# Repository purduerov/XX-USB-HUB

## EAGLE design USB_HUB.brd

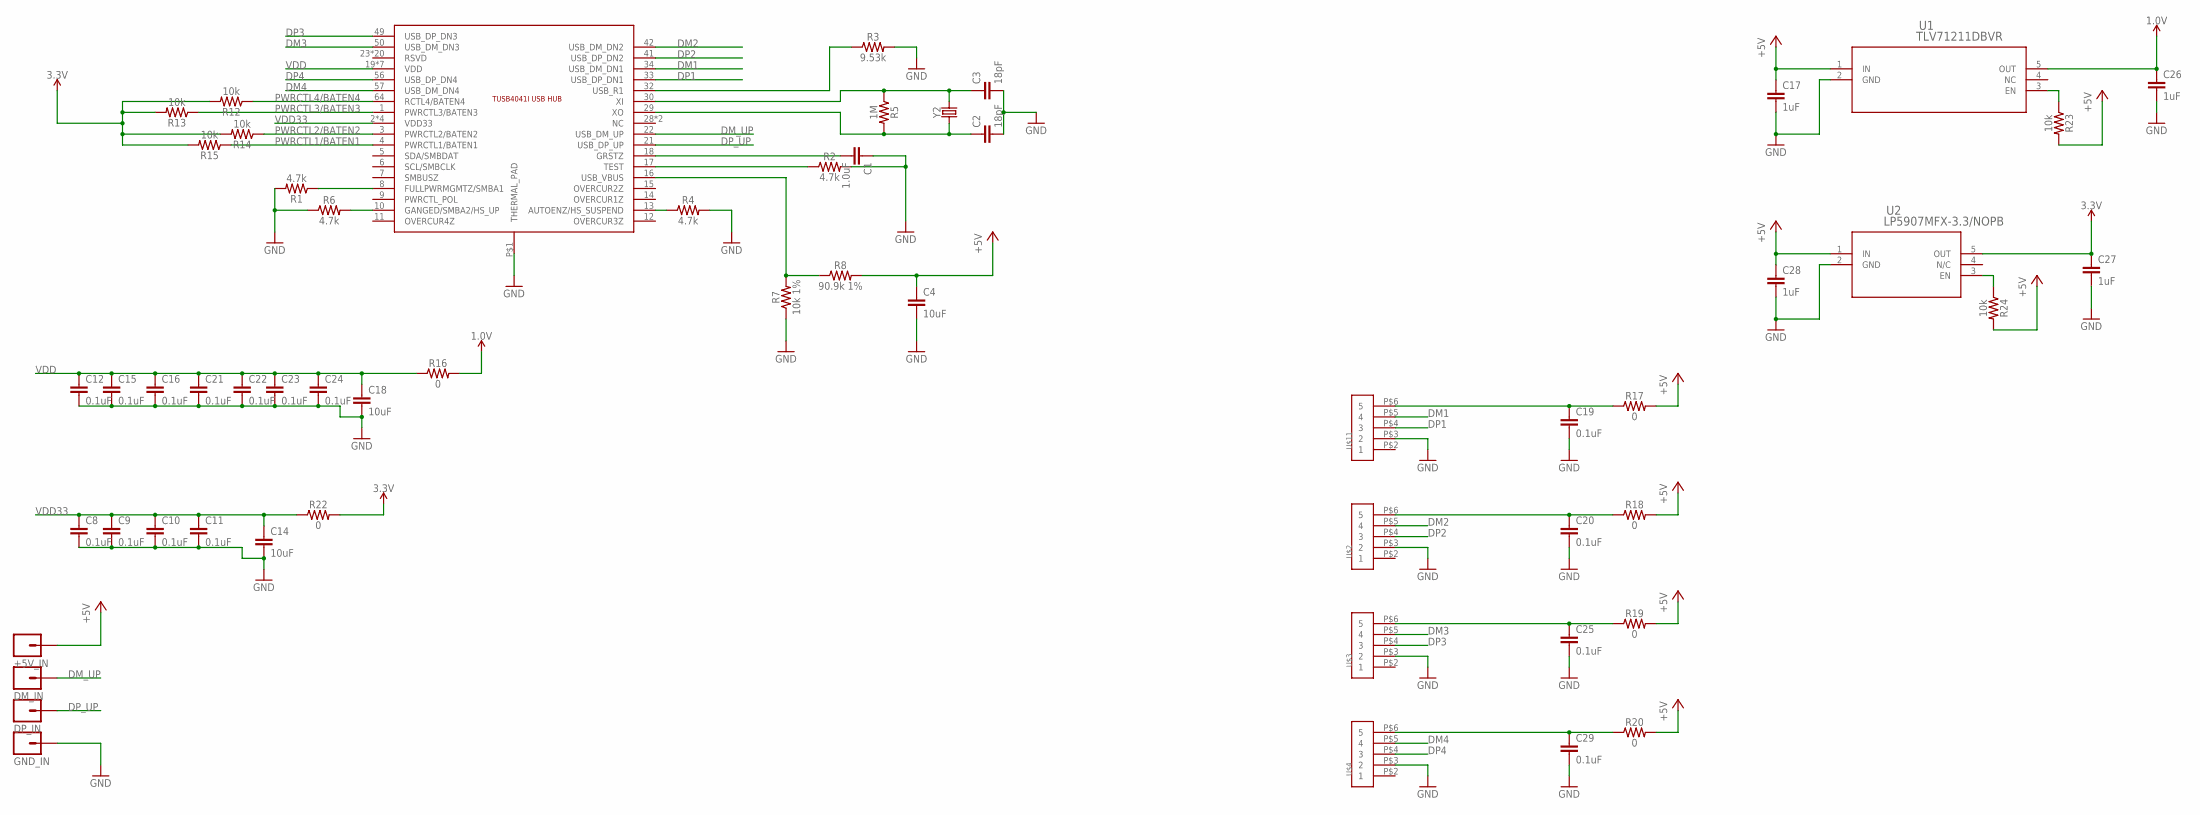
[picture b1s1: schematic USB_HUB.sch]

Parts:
+5V_IN: M01PTH; 1X01
C1: 1.0uF; 0603
C2, C3: 18pF; 0603
C4, C14, C18: 10uF; 0805
C8, C9, C10, C11, C12, C15, C16, C19, C20, C21, C22, C23, C24, C25, C29: 0.1uF; 0603
C17, C26, C27, C28: 1uF; 0603
DM_IN: M01PTH; 1X01
DP_IN: M01PTH; 1X01
GND_IN: M01PTH; 1X01
R1, R2, R4, R6: 4.7k; 0603
R3: 9.53k; 0603
R5: 1M; 0603
R7: 10k 1%; 0603
R8: 90.9k 1%; 0603
R12, R13, R14, R15, R23, R24: 10k; 0603
R16, R17, R18, R19, R20, R22: 0; 0805
U1: TLV71211DBVR; DBV5
U2: LP5907MFX-3.3/NOPB; DBV5
U$1: TUSB4041I
U$2, U$3, U$4, U$11: T2I5P
Y2: CRYSTALPTH-HC49US; HC49US

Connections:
1.0V: C26.1, R16.2, U1.5 (OUT)
3.3V: C27.1, R12.2, R13.2, R14.2, R15.2, R22.2, U2.5 (OUT)
+5V: +5V_IN.1, C4.1, C17.1, C28.1, R8.2, R17.2, R18.2, R19.2, R20.2, R23.2, R24.2, U1.1 (IN), U2.1 (IN)
DM1: U$1.34 (USB_DM_DN1), U$11.P$5 (4)
DM2: U$1.42 (USB_DM_DN2), U$2.P$5 (4)
DM3: U$1.50 (USB_DM_DN3), U$3.P$5 (4)
DM4: U$1.57 (USB_DM_DN4), U$4.P$5 (4)
DM_UP: DM_IN.1, U$1.22 (USB_DM_UP)
DP1: U$1.33 (USB_DP_DN1), U$11.P$4 (3)
DP2: U$1.41 (USB_DP_DN2), U$2.P$4 (3)
DP3: U$1.49 (USB_DP_DN3), U$3.P$4 (3)
DP4: U$1.56 (USB_DP_DN4), U$4.P$4 (3)
DP_UP: DP_IN.1, U$1.21 (USB_DP_UP)
GND: C1.1, C2.2, C3.2, C4.2, C8.2, C9.2, C10.2, C11.2, C12.2, C14.2, C15.2, C16.2, C17.2, C18.2, C19.2, C20.2, C21.2, C22.2, C23.2, C24.2, C25.2, C26.2, C27.2, C28.2, C29.2, GND_IN.1, R1.2, R2.2, R3.2, R4.2, R6.1, R7.1, U1.2 (GND), U2.2 (GND), U$1.P$1 (THERMAL_PAD), U$2.P$3 (2), U$3.P$3 (2), U$4.P$3 (2), U$11.P$3 (2)
unnamed: C1.2, U$1.18 (GRSTZ)
unnamed: R3.1, U$1.32 (USB_R1)
unnamed: R2.1, U$1.17 (TEST)
unnamed: R4.1, U$1.13 (AUTOENZ/HS_SUSPEND)
unnamed: C3.1, R5.1, U$1.30 (XI), Y2.2
unnamed: C2.1, R5.2, U$1.29 (XO), Y2.1
unnamed: R1.1, U$1.8 (FULLPWRMGMTZ/SMBA1)
unnamed: R6.2, U$1.10 (GANGED/SMBA2/HS_UP)
unnamed: R7.2, R8.1, U$1.16 (USB_VBUS)
unnamed: R23.1, U1.3 (EN)
unnamed: R24.1, U2.3 (EN)
PWRCTL1/BATEN1: R15.1, U$1.4 (PWRCTL1/BATEN1)
PWRCTL2/BATEN2: R14.1, U$1.3 (PWRCTL2/BATEN2)
PWRCTL3/BATEN3: R13.1, U$1.1 (PWRCTL3/BATEN3)
PWRCTL4/BATEN4: R12.1, U$1.64 (RCTL4/BATEN4)
USB1_+5V: C19.1, R17.1, U$11.P$6 (5)
USB2_+5V: C20.1, R18.1, U$2.P$6 (5)
USB3_+5V: C25.1, R19.1, U$3.P$6 (5)
USB4_+5V: C29.1, R20.1, U$4.P$6 (5)
VDD: C12.1, C15.1, C16.1, C18.1, C21.1, C22.1, C23.1, C24.1, R16.1, U$1.19 (VDD), U$1.25 (VDD), U$1.37 (VDD), U$1.45 (VDD), U$1.53 (VDD), U$1.60 (VDD), U$1.63 (VDD)
VDD33: C8.1, C9.1, C10.1, C11.1, C14.1, R22.1, U$1.2 (VDD33), U$1.20 (VDD33), U$1.31 (VDD33), U$1.48 (VDD33)

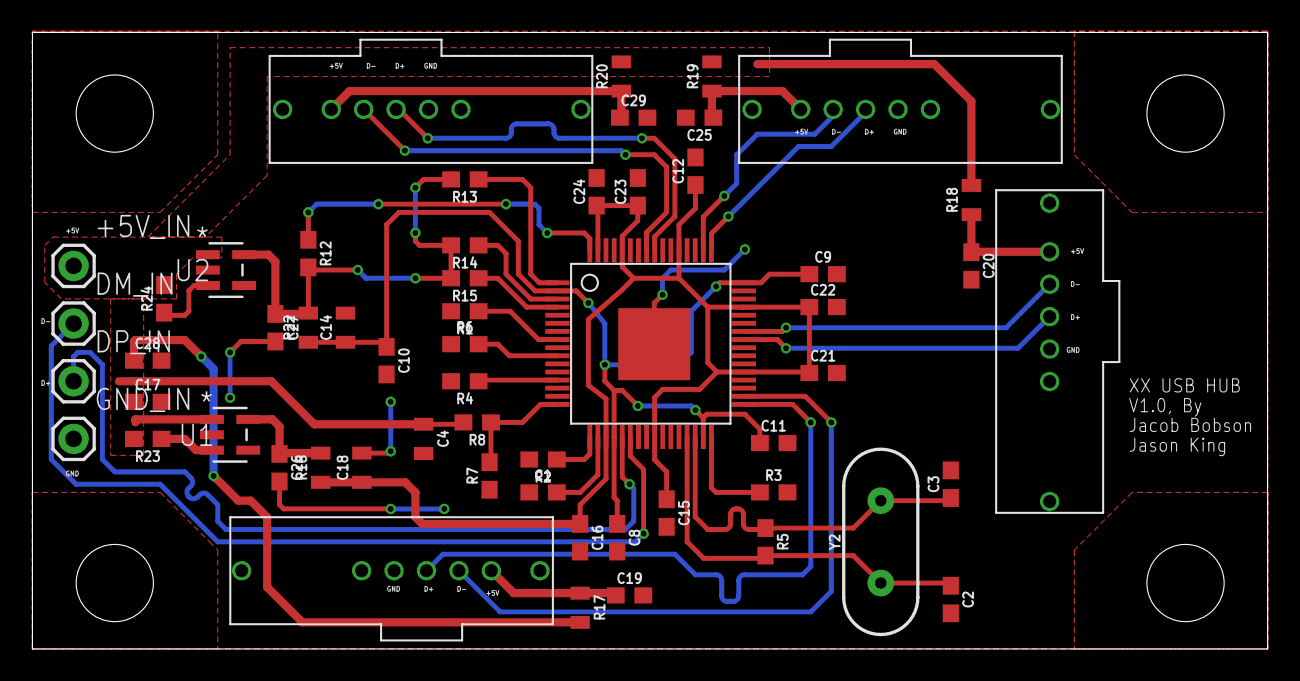
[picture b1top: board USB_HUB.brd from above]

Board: 2 copper layers, 76.2 x 38.0 mm, 57 parts (0 on the bottom side), 35 nets.

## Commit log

2018-02-15 Added board
2018-02-19 Fixed
2018-02-19 this should work..
2018-02-19 Added silkcreen and identifiers for easier construction
2018-03-08 Added issues

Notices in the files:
parts and their libraries:
SparkFun-Capacitors: Licensing: Creative Commons ShareAlike 4.0 International - https://creativecommons.org/licenses/by-sa/4.0
